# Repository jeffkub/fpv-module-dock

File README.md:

# fpv-module-dock
Docking station for Fatshark style FPV modules

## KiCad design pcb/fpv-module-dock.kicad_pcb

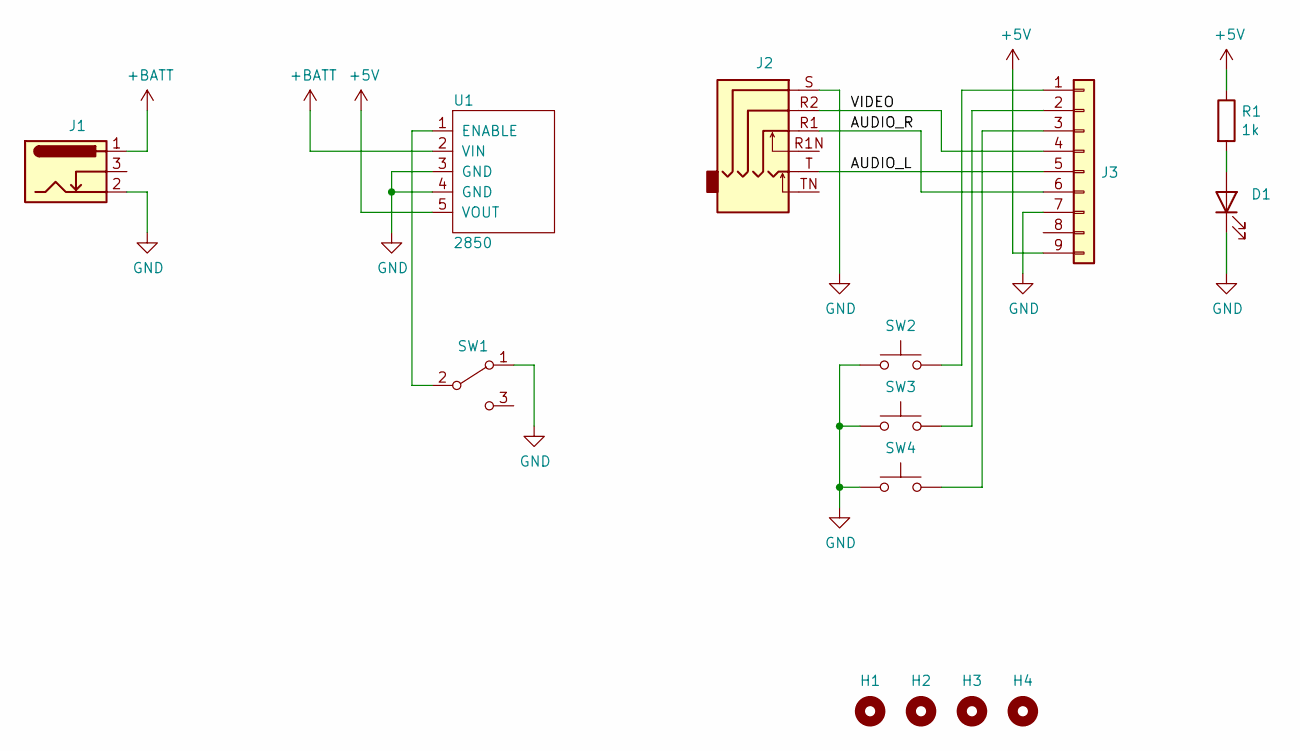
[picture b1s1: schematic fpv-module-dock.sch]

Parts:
D1: LED; LED_0805_2012Metric_Pad1.15x1.40mm_HandSolder; Digi-Key Part Number 754-1132-1-ND
H1, H2, H3, H4: MountingHole; MountingHole_3.2mm_M3
J1: Barrel_Jack_Switch; PJ-051AH; Digi-Key Part Number CP-051AH-ND‎
J2: AudioJack4_SwitchTR1; SJ-43516-SMT; Digi-Key Part Number CP-43515TSSJCT-ND‎
J3: Conn_01x09; PinSocket_1x09_P2.54mm_Vertical; Digi-Key Part Number S7042-ND‎
R1: 1k; R_0805_2012Metric_Pad1.15x1.40mm_HandSolder; Digi-Key Part Number 311-1.00KCRCT-ND
SW1: SW_SPDT; OS102011MA1QN1; Digi-Key Part Number CKN9559-ND‎
SW2, SW3, SW4: SW_Push; SW_Tactile_SPST_Angled_PTS645Vx83-2LFS; Digi-Key Part Number 450-1642-ND‎
U1: 2850; Digi-Key Part Number 2183-2850-ND

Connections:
+5V: J3.9, R1.1, U1.5 (VOUT)
+BATT: J1.1, U1.2 (VIN)
/AUDIO_L: J2.T, J3.5
/AUDIO_R: J2.R1, J3.6
/VIDEO: J2.R2, J3.4
GND: D1.1 (K), J1.2, J2.S, J3.7, SW1.1 (A), SW2.1, SW3.1, SW4.1, U1.3 (GND), U1.4 (GND)
unnamed: D1.2 (A), R1.2
unnamed: J3.1, SW2.2
unnamed: J3.2, SW3.2
unnamed: J3.3, SW4.2
unnamed: SW1.2 (B), U1.1 (ENABLE)

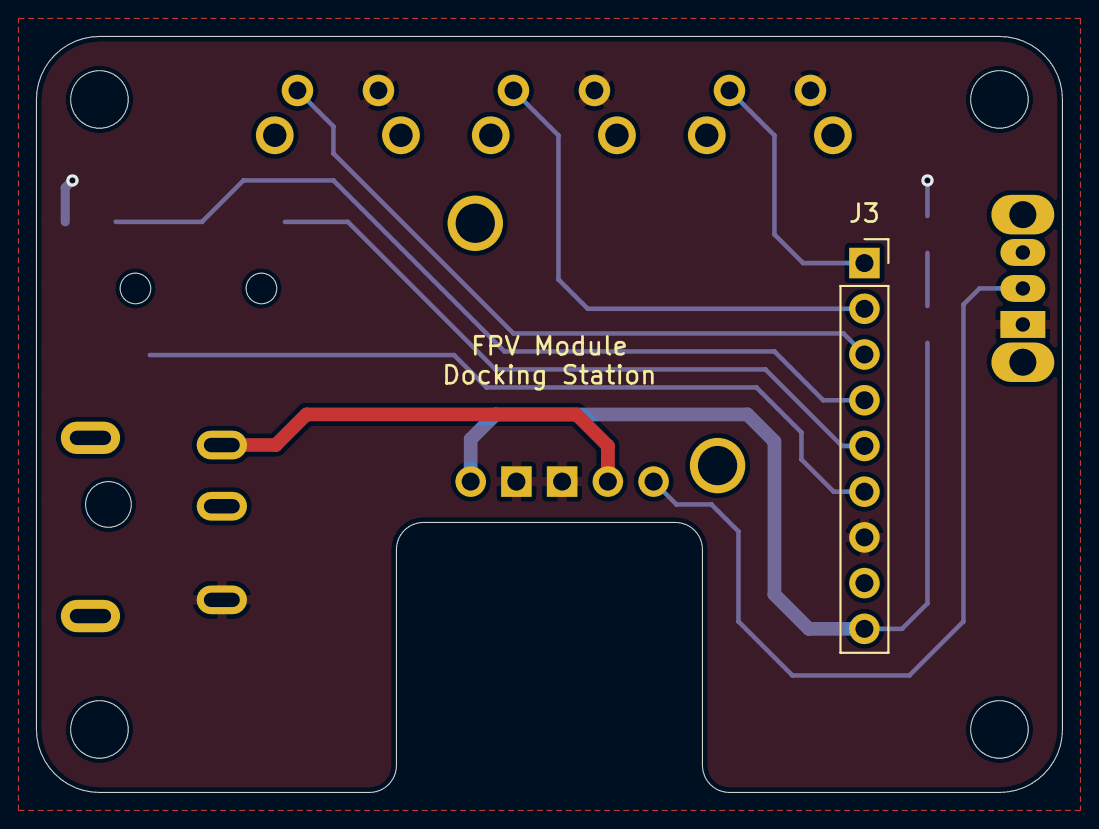
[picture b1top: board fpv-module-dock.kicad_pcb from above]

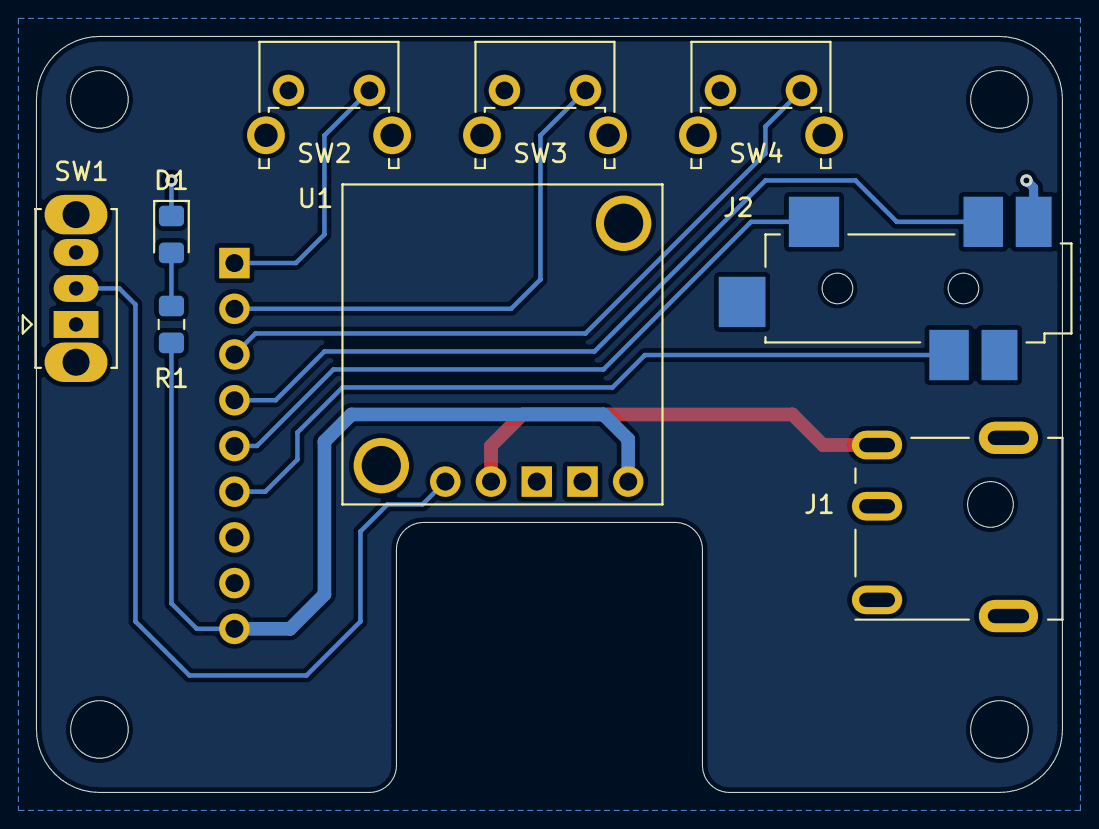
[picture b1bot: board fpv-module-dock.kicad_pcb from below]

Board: 2 copper layers, 57.0 x 42.0 mm, 14 parts (9 on the bottom side), 11 nets.

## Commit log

2021-02-07 Initial commit of KiCad project
2021-02-08 Schematic complete, exported netlist to layout
2021-02-08 Working on layout
2021-02-09 Added 3D models, completed layout
2021-02-10 Added power LED
2021-02-10 Minor PCB tweaks
